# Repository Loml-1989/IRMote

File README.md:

# IRMote
A small IR remote built using a XIAO ESP32 C3. Point a remote at it, press a button, and it remembers the signal. Press another button and it re emit it back out.

## Gallery
## Final PCB front

## Final PCB back

### PCB

### Schematics

### Case

### Keychain

https://cad.onshape.com/documents/72053f8b7099b1ee551be8fa/w/c9c509dfd2f6c74695d77e8d/e/00c4d274837c6173d7a47207?renderMode=0&uiState=6ad7b619d79b6117422c9eec

## Buttons
| Button | What it does                     |
| ------ | -------------------------------- |
| Left   | Capture an IR signal             |
| Middle | Reset (forget the stored signal) |
| Right  | Re-emit the stored signal        |

## Hardware
- Seeed XIAO ESP32 C3
- TSOP38238 IR receiver
- IR LED driven by a BC547
- 3 push buttons
- Slide switch
## Building it
1. Install the ESP32 board package for Arduino and pick the XIAO esp32 c3.
2. Open `ir_capture_replay.ino`.
3. Upload.
## Firmware
The firmware currently only prints the data in the serial moniter when you capture a package. I have plans to add some sort of android support like maybe use the bluetooth or wifi in some way to control it from phone but I have to first make sure that the core function of this works thats why I havent done that.
## Using it
1. Power it on.
2. Press the left button, then use a remote at the receiver within a 10 seconds.
3. Press the right button to replay it at whatever you want to control.
4. Middle button wipes it if you want to start over.

Open the Serial Monitor at 115200 baud if you want to see data.
## Notes
- Nothing is saved to flash, so the signal is gone when you power off.
- Range is pretty short.
- Also the case is not incomplete! It is a open style. There are walls under the PCB where you stick double sided tape.

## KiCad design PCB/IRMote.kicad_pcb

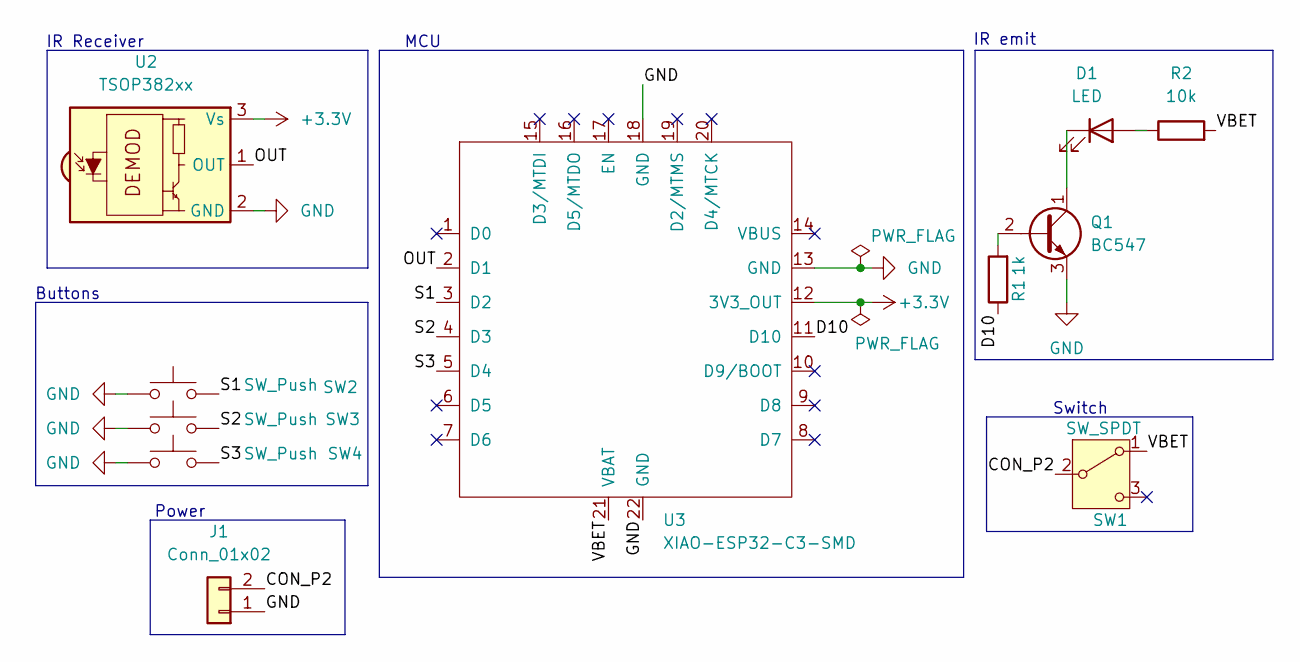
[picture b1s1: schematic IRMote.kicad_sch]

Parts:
D1: LED; LED_D5.0mm_Horizontal_O1.27mm_Z3.0mm_IRBlack
J1: Conn_01x02; JST_PH_S2B-PH-K_1x02_P2.00mm_Horizontal
Q1: BC547; TO-92_Inline_Horizontal1
R1: 1k; R_Axial_DIN0207_L6.3mm_D2.5mm_P10.16mm_Horizontal
R2: 10k; R_Axial_DIN0207_L6.3mm_D2.5mm_P10.16mm_Horizontal
SW1: SW_SPDT; SW_Slide_SPDT_Straight_CK_OS102011MS2Q
SW2, SW3, SW4: SW_Push; SW_PUSH_6mm
U2: TSOP382xx; Vishay_MINICAST-3Pin
U3: XIAO-ESP32-C3-SMD

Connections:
+3.3V: U2.3 (Vs), U3.12 (3V3_OUT)
/CON_P2: J1.2, SW1.2 (B)
/D10: R1.1, U3.11 (D10)
/OUT: U2.1 (OUT), U3.2 (D1)
/S1: SW2.2, U3.3 (D2)
/S2: SW3.2, U3.4 (D3)
/S3: SW4.2, U3.5 (D4)
/VBET: R2.2, SW1.1 (A), U3.21 (VBAT)
GND: J1.1, Q1.3 (E), SW2.1, SW3.1, SW4.1, U2.2 (GND), U3.13 (GND), U3.18 (GND), U3.22 (GND)
unnamed: D1.2 (A), R2.1
unnamed: D1.1 (K), Q1.1 (C)
unnamed: Q1.2 (B), R1.2

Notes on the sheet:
MCU
IR emit
Power
Buttons
Switch
IR Receiver

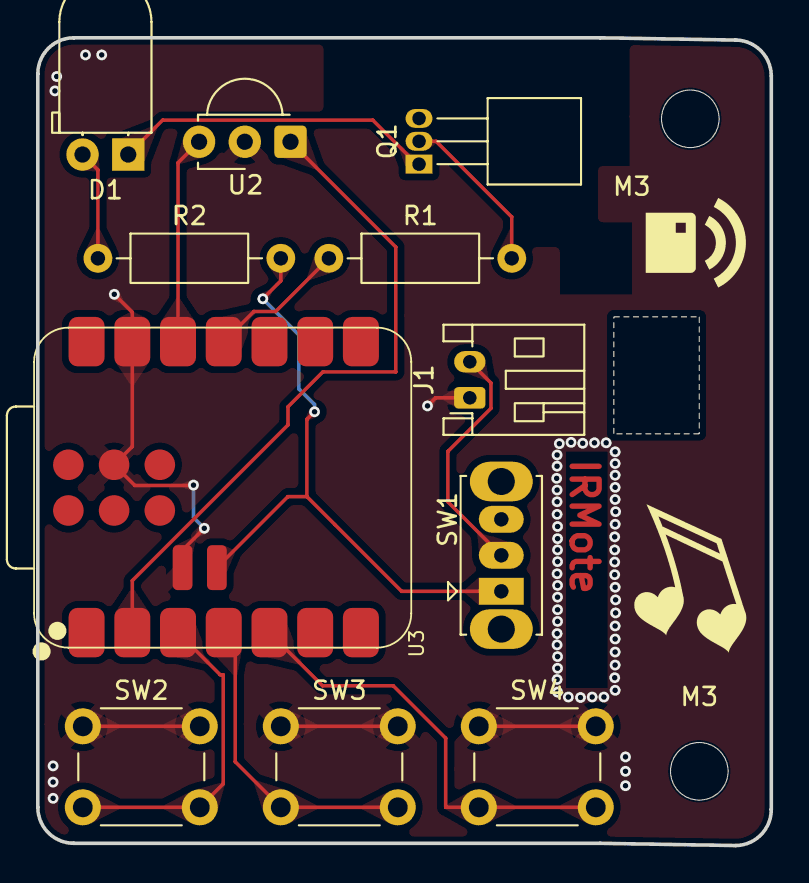
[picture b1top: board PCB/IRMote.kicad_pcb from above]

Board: 2 copper layers, 40.8 x 44.9 mm, 13 parts (0 on the bottom side), 12 nets.

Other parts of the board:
M3, M3#2: MountingHole_3.2mm_M3

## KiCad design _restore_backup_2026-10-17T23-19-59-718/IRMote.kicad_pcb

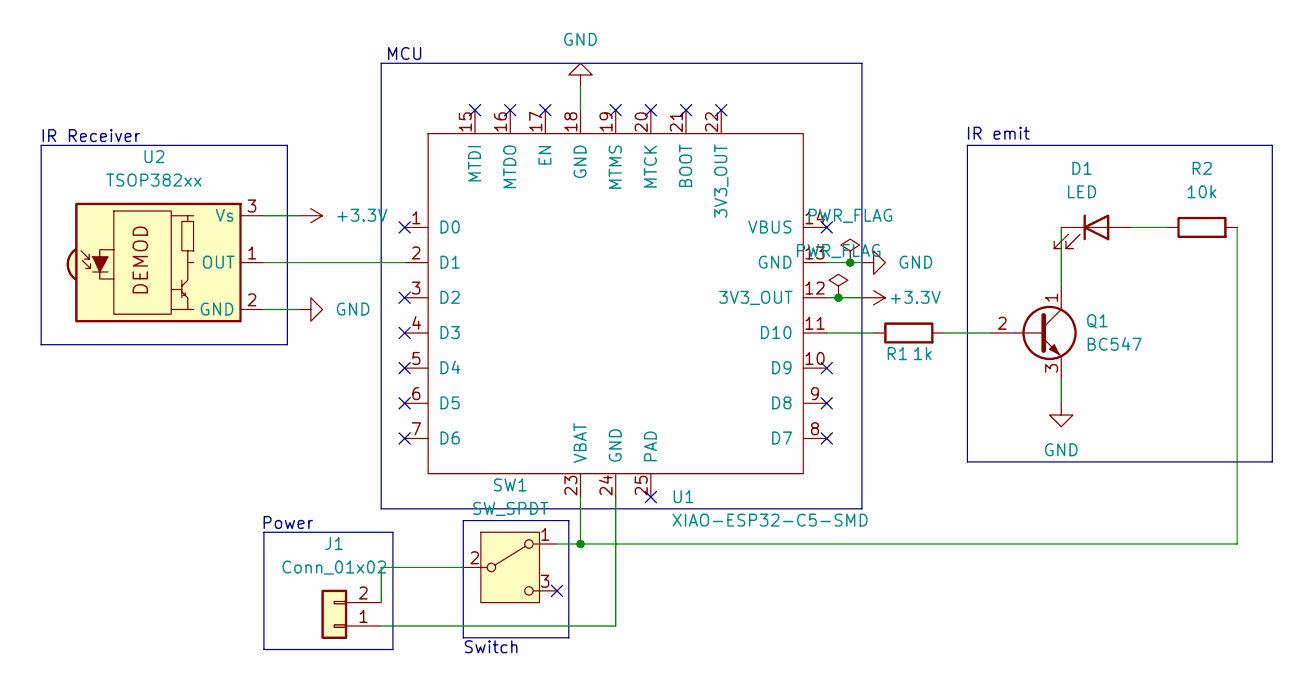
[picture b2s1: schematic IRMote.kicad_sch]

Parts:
D1: LED; LED_D5.0mm
J1: Conn_01x02; JST_PH_B2B-PH-K_1x02_P2.00mm_Vertical
Q1: BC547; TO-92_Inline
R1: 1k; R_Axial_DIN0207_L6.3mm_D2.5mm_P10.16mm_Horizontal
R2: 10k; R_Axial_DIN0207_L6.3mm_D2.5mm_P10.16mm_Horizontal
SW1: SW_SPDT; SW_Slide_SPDT_Straight_CK_OS102011MS2Q
U1: XIAO-ESP32-C5-SMD
U2: TSOP382xx; Vishay_MINICAST-3Pin

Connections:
+3.3V: U1.12 (3V3_OUT), U2.3 (Vs)
GND: Q1.3 (E), U1.13 (GND), U1.18 (GND), U2.2 (GND)
unnamed: D1.2 (A), R2.1
unnamed: D1.1 (K), Q1.1 (C)
unnamed: J1.1, U1.24 (GND)
unnamed: J1.2, SW1.2 (B)
unnamed: Q1.2 (B), R1.2
unnamed: R2.2, SW1.1 (A), U1.23 (VBAT)
unnamed: U1.2 (D1), U2.1 (OUT)
unnamed: R1.1, U1.11 (D10)

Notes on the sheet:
MCU
IR emit
Power
Switch
IR Receiver

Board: 2 copper layers, 8 parts (0 on the bottom side), 10 nets, no tracks yet.
